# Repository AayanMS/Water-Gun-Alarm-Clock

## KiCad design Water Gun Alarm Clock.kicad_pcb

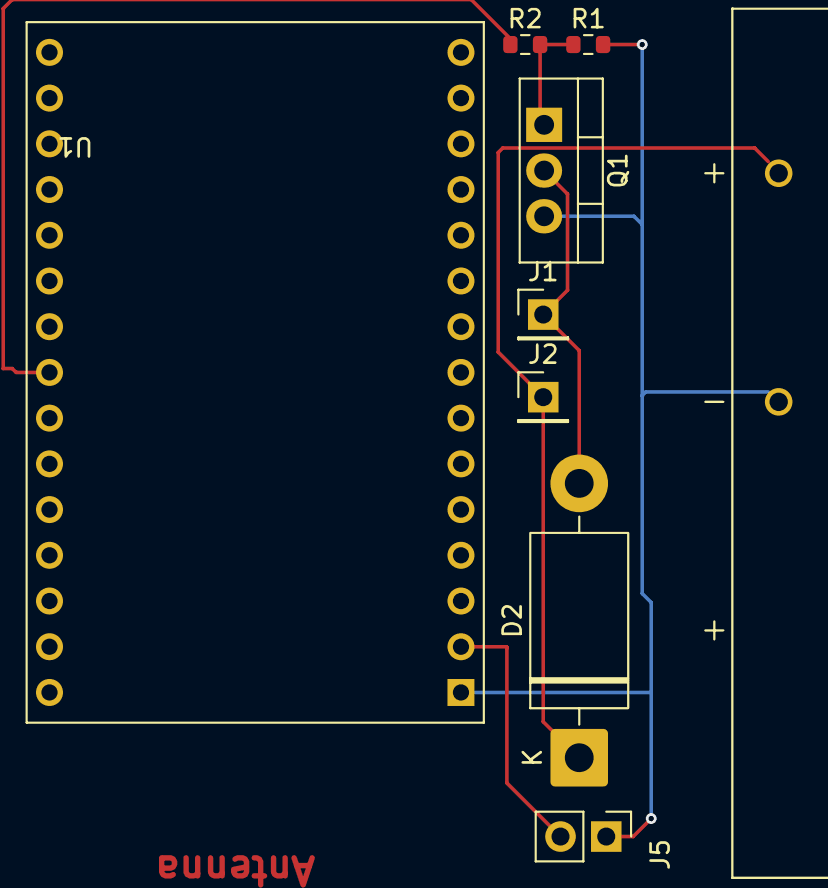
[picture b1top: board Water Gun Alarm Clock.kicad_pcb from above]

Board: 2 copper layers, 9 parts (0 on the bottom side), 7 nets.

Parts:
BT1: 4.5V; 3xAA Battery Holder
D2: 1N5822; D_DO-201AD_P15.24mm_Horizontal
J1: PNT; PinHeader_1x01_P2.54mm_Vertical
J2: PPT; PinHeader_1x01_P2.54mm_Vertical
J5: External Pow.; PinHeader_1x02_P2.54mm_Vertical
Q1: IRLB8721PBF; TO-220-3_Vertical
R1: 10K; R_0603_1608Metric
R2: 1k; R_0603_1608Metric
U1: ESP32-C3-DevKitM-1

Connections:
GND: J5.1, Q1.3 (S), R1.2, U1.1 (GND), U1.6 (GND), U1.8 (GND), U1.12 (GND), U1.15 (GND), U1.16 (GND), U1.19 (GND), U1.24 (GND), U1.27 (GND), U1.30 (GND)
unnamed: D2.1 (K), J2.1 (Pin_1_1)
unnamed: D2.2 (A), J1.1 (Pin_1_1), Q1.2 (D)
unnamed: J5.2, U1.2 (3V3), U1.3 (3V3)
unnamed: Q1.1 (G), R1.1, R2.2
unnamed: U1.13 (5V), U1.14 (5V)
unnamed: R2.1, U1.23 (IO7)
